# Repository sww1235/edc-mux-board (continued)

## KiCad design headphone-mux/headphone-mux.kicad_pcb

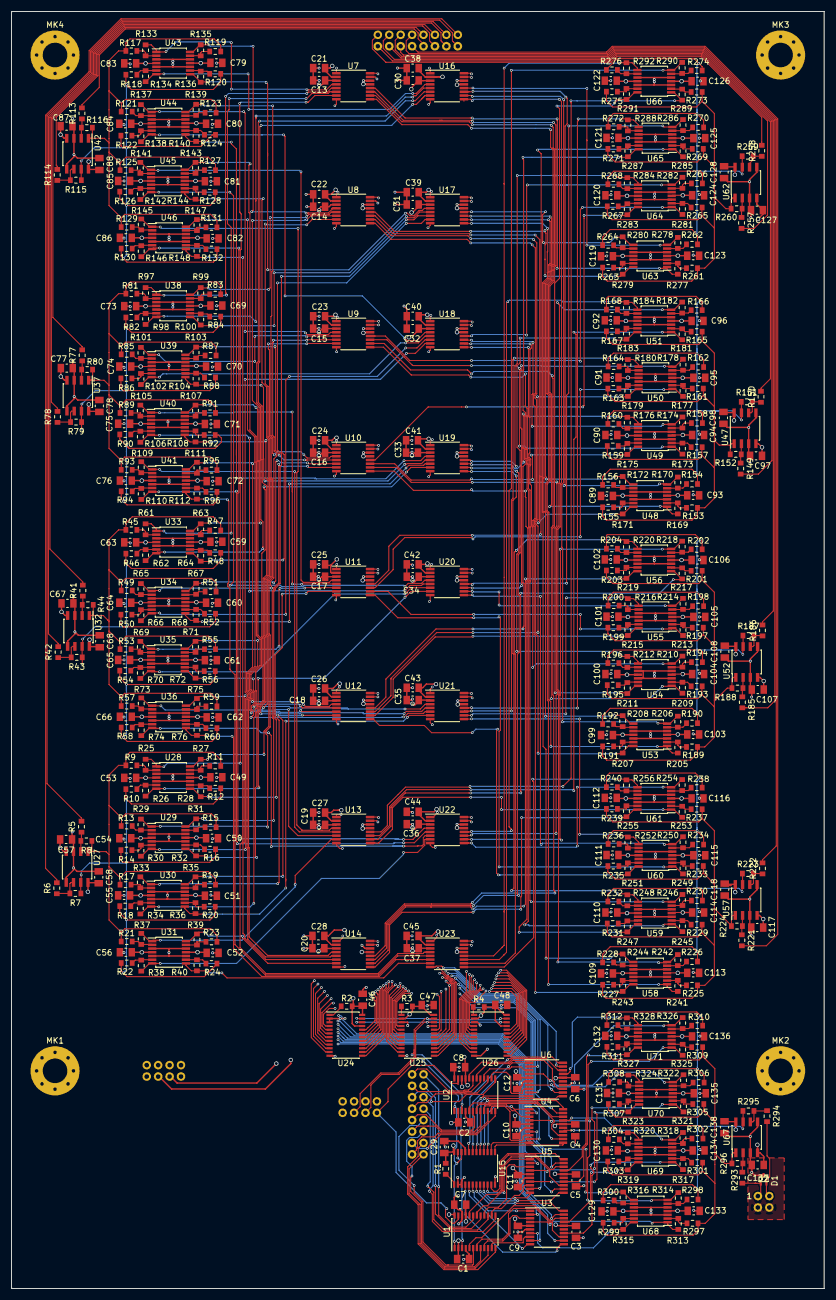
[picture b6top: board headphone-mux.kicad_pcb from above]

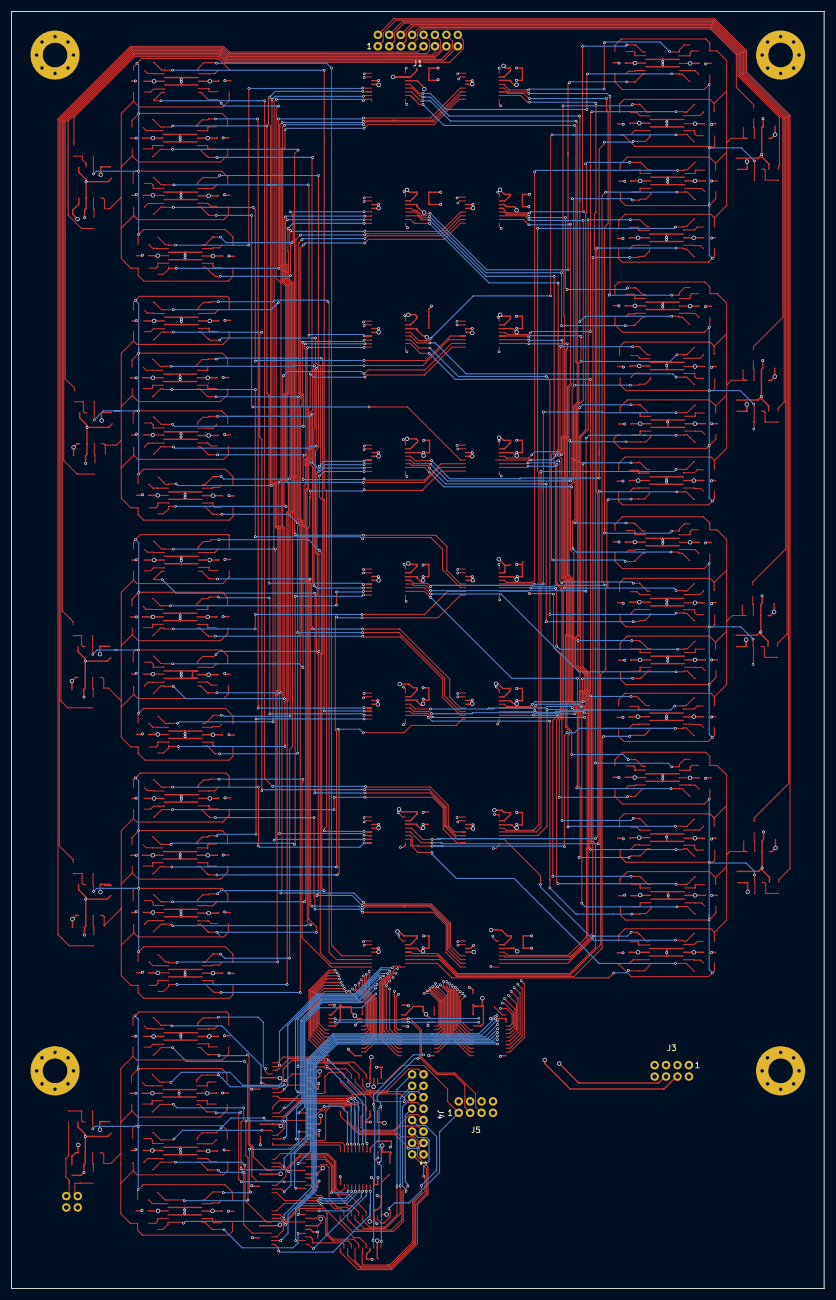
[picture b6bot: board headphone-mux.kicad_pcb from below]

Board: 4 copper layers, 142.2 x 223.5 mm, 547 parts (4 on the bottom side), 466 nets.

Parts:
C1, C2, C3, C4, C5, C6, C7, C8, C9, C10, C11, C12, C13, C14, C15, C16, C17, C18, C19, C20, C21, C22, C23, C24, C25, C26, C27, C28, C29, C30, C31, C32, C33, C34, C35, C36, C37, C38, C39, C40, C41, C42, C43, C44, C45, C46, C47, C48, C49, C50, C51, C52, C53, C54, C55, C56, C57, C58, C59, C60, C61, C62, C63, C64, C65, C66, C67, C68, C69, C70, C71, C72, C73, C74, C75, C76, C77, C78, C79, C80, C81, C82, C83, C84, C85, C86, C87, C88, C89, C90, C91, C92, C93, C94, C95, C96, C97, C98, C99, C100, C101, C102, C103, C104, C105, C106, C107, C108, C109, C110, C111, C112, C113, C114, C115, C116, C117, C118, C119, C120, C121, C122, C123, C124, C125, C126, C127, C128, C129, C130, C131, C132, C133, C134, C135, C136, C137, C138: 0.1uF; C_0805_2012Metric_Pad1.15x1.50mm_HandSolder
D1: 0582BQ; SC-75_3L
J1: Audio-Input; DF11-16DS-2DSA
J2: Mixer Audio In; DF11-4DP-2DSA
J3: Power Input; DF11-8DS-2DSA
J4: Audio Output; DF11-16DS-2DSA
J5: I2C and Reset; DF11-8DS-2DSA
MK1, MK2, MK3, MK4: Mounting_Hole_PAD; MountingHole_4.3mm_M4_Pad_Via
R1, R2, R3, R4: 10kΩ; R_0603_1608Metric_Pad0.84x1.00mm_HandSolder
R5, R6, R7, R8, R9, R10, R11, R12, R13, R14, R15, R16, R17, R18, R19, R20, R21, R22, R23, R24, R25, R26, R27, R28, R29, R30, R31, R32, R33, R34, R35, R36, R37, R38, R39, R40, R41, R42, R43, R44, R45, R46, R47, R48, R49, R50, R51, R52, R53, R54, R55, R56, R57, R58, R59, R60, R61, R62, R63, R64, R65, R66, R67, R68, R69, R70, R71, R72, R73, R74, R75, R76, R77, R78, R79, R80, R81, R82, R83, R84, R85, R86, R87, R88, R89, R90, R91, R92, R93, R94, R95, R96, R97, R98, R99, R100, R101, R102, R103, R104, R105, R106, R107, R108, R109, R110, R111, R112, R113, R114, R115, R116, R117, R118, R119, R120, R121, R122, R123, R124, R125, R126, R127, R128, R129, R130, R131, R132, R133, R134, R135, R136, R137, R138, R139, R140, R141, R142, R143, R144, R145, R146, R147, R148, R149, R150, R151, R152, R153, R154, R155, R156, R157, R158, R159, R160, R161, R162, R163, R164, R165, R166, R167, R168, R169, R170, R171, R172, R173, R174, R175, R176, R177, R178, R179, R180, R181, R182, R183, R184, R185, R186, R187, R188, R189, R190, R191, R192, R193, R194, R195, R196, R197, R198, R199, R200, R201, R202, R203, R204, R205, R206, R207, R208, R209, R210, R211, R212, R213, R214, R215, R216, R217, R218, R219, R220, R221, R222, R223, R224, R225, R226, R227, R228, R229, R230, R231, R232, R233, R234, R235, R236, R237, R238, R239, R240, R241, R242, R243, R244, R245, R246, R247, R248, R249, R250, R251, R252, R253, R254, R255, R256, R257, R258, R259, R260, R261, R262, R263, R264, R265, R266, R267, R268, R269, R270, R271, R272, R273, R274, R275, R276, R277, R278, R279, R280, R281, R282, R283, R284, R285, R286, R287, R288, R289, R290, R291, R292, R293, R294, R295, R296, R297, R298, R299, R300, R301, R302, R303, R304, R305, R306, R307, R308, R309, R310, R311, R312, R313, R314, R315, R316, R317, R318, R319, R320, R321, R322, R323, R324, R325, R326, R327, R328: 100kΩ; R_0603_1608Metric_Pad0.84x1.00mm_HandSolder
U1, U2: ADG715; TSSOP-24_4.4x7.8mm_P0.65mm
U3, U4, U5, U6: ADG734; TSSOP-20_4.4x6.5mm_P0.65mm
U7, U8, U9, U10, U11, U12, U13, U14, U16, U17, U18, U19, U20, U21, U22, U23: ADG708; TSSOP-16_4.4x5mm_P0.65mm
U15, U24, U25, U26: TCA9555; TSSOP-24_4.4x7.8mm_P0.65mm
U27, U32, U37, U42, U47, U52, U57, U62, U67: OPA1602; SOIC-8_3.9x4.9mm_P1.27mm
U28, U29, U30, U31, U33, U34, U35, U36, U38, U39, U40, U41, U43, U44, U45, U46, U48, U49, U50, U51, U53, U54, U55, U56, U58, U59, U60, U61, U63, U64, U65, U66, U68, U69, U70, U71: OPA1604; TSSOP-14_4.4x5mm_P0.65mm

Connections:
+2V5: C1.2, C2.2, C3.2, C4.2, C5.2, C6.2, C21.1, C22.1, C23.1, C24.1, C25.1, C26.1, C27.1, C28.1, C29.2, C38.1, C39.1, C40.1, C41.1, C42.1, C43.1, C44.1, C45.1, C46.2, C47.2, C48.2, J3.4, R1.1, R2.1, R3.1, R4.1, U1.2, U1.24, U2.2, U2.22, U3.16, U4.16, U5.16, U6.16, U7.2, U7.13, U8.2, U8.13, U9.2, U9.13, U10.2, U10.13, U11.2, U11.13, U12.2, U12.13, U13.2, U13.13, U14.2, U14.13, U15.24, U16.2, U16.13, U17.2, U17.13, U18.2, U18.13, U19.2, U19.13, U20.2, U20.13, U21.2, U21.13, U22.2, U22.13, U23.2, U23.13, U24.21, U24.24, U25.2, U25.24, U26.2, U26.21, U26.24
+12VA: C53.2, C54.2, C55.2, C56.2, C58.2, C63.2, C64.2, C65.2, C66.2, C68.2, C73.2, C74.2, C75.2, C76.2, C78.2, C83.2, C84.2, C85.2, C86.2, C88.2, C93.2, C94.2, C95.2, C96.2, C98.2, C103.2, C104.2, C105.2, C106.2, C108.2, C113.2, C114.2, C115.2, C116.2, C118.2, C123.2, C124.2, C125.2, C126.2, C128.2, C133.2, C134.2, C135.2, C136.2, C138.2, J3.2, U27.8, U28.4, U29.4, U30.4, U31.4, U32.8, U33.4, U34.4, U35.4, U36.4, U37.8, U38.4, U39.4, U40.4, U41.4, U42.8, U43.4, U44.4, U45.4, U46.4, U47.8, U48.4, U49.4, U50.4, U51.4, U52.8, U53.4, U54.4, U55.4, U56.4, U57.8, U58.4, U59.4, U60.4, U61.4, U62.8, U63.4, U64.4, U65.4, U66.4, U67.8, U68.4, U69.4, U70.4, U71.4
-2.5V: C7.1, C8.1, C9.1, C10.1, C11.1, C12.1, C13.2, C14.2, C15.2, C16.2, C17.2, C18.2, C19.2, C20.2, C30.2, C31.2, C32.2, C33.2, C34.2, C35.2, C36.2, C37.2, J3.6, U1.21, U2.21, U3.5, U4.5, U5.5, U6.5, U7.3, U8.3, U9.3, U10.3, U11.3, U12.3, U13.3, U14.3, U16.3, U17.3, U18.3, U19.3, U20.3, U21.3, U22.3, U23.3
-12VA: C49.2, C50.2, C51.2, C52.2, C57.2, C59.2, C60.2, C61.2, C62.2, C67.2, C69.2, C70.2, C71.2, C72.2, C77.2, C79.2, C80.2, C81.2, C82.2, C87.2, C89.2, C90.2, C91.2, C92.2, C97.2, C99.2, C100.2, C101.2, C102.2, C107.2, C109.2, C110.2, C111.2, C112.2, C117.2, C119.2, C120.2, C121.2, C122.2, C127.2, C129.2, C130.2, C131.2, C132.2, C137.2, J3.8, U27.4, U28.11, U29.11, U30.11, U31.11, U32.4, U33.11, U34.11, U35.11, U36.11, U37.4, U38.11, U39.11, U40.11, U41.11, U42.4, U43.11, U44.11, U45.11, U46.11, U47.4, U48.11, U49.11, U50.11, U51.11, U52.4, U53.11, U54.11, U55.11, U56.11, U57.4, U58.11, U59.11, U60.11, U61.11, U62.4, U63.11, U64.11, U65.11, U66.11, U67.4, U68.11, U69.11, U70.11, U71.11
/2v5-SCL-0: J5.3, U1.1, U2.1, U15.22, U24.22, U25.22, U26.22
/2v5-SDA-0: J5.5, U1.3, U2.3, U15.23, U24.23, U25.23, U26.23
/HEADSET-AUDIO-SOURCE-L-0: J1.1, R5.2
/HEADSET-AUDIO-SOURCE-L-1: J1.3, R41.2
/HEADSET-AUDIO-SOURCE-L-2: J1.5, R77.2
/HEADSET-AUDIO-SOURCE-L-3: J1.7, R113.2
/HEADSET-AUDIO-SOURCE-L-4: J1.15, R257.2
/HEADSET-AUDIO-SOURCE-L-5: J1.13, R149.2
/HEADSET-AUDIO-SOURCE-L-6: J1.11, R185.2
/HEADSET-AUDIO-SOURCE-L-7: J1.9, R221.2
/HEADSET-AUDIO-SOURCE-R-0: J1.2, R6.2
/HEADSET-AUDIO-SOURCE-R-1: J1.4, R42.2
/HEADSET-AUDIO-SOURCE-R-2: J1.6, R78.2
/HEADSET-AUDIO-SOURCE-R-3: J1.8, R114.2
/HEADSET-AUDIO-SOURCE-R-4: J1.16, R258.2
/HEADSET-AUDIO-SOURCE-R-5: J1.14, R150.2
/HEADSET-AUDIO-SOURCE-R-6: J1.12, R186.2
/HEADSET-AUDIO-SOURCE-R-7: J1.10, R222.2
/Headset Audio Out Mux Switching/DEV0_L_0: R25.1, U7.7, U28.1
/Headset Audio Out Mux Switching/DEV0_L_1: R27.1, U8.7, U28.14
/Headset Audio Out Mux Switching/DEV0_L_2: R29.1, U9.7, U29.1
/Headset Audio Out Mux Switching/DEV0_L_3: R31.1, U10.7, U29.14
/Headset Audio Out Mux Switching/DEV0_L_4: R33.1, U11.7, U30.1
/Headset Audio Out Mux Switching/DEV0_L_5: R35.1, U12.7, U30.14
/Headset Audio Out Mux Switching/DEV0_L_6: R37.1, U13.7, U31.1
/Headset Audio Out Mux Switching/DEV0_L_7: R39.1, U14.7, U31.14
/Headset Audio Out Mux Switching/DEV0_R_0: R26.1, U16.7, U28.7
/Headset Audio Out Mux Switching/DEV0_R_1: R28.1, U17.7, U28.8
/Headset Audio Out Mux Switching/DEV0_R_2: R30.1, U18.7, U29.7
/Headset Audio Out Mux Switching/DEV0_R_3: R32.1, U19.7, U29.8
/Headset Audio Out Mux Switching/DEV0_R_4: R34.1, U20.7, U30.7
/Headset Audio Out Mux Switching/DEV0_R_5: R36.1, U21.7, U30.8
/Headset Audio Out Mux Switching/DEV0_R_6: R38.1, U22.7, U31.7
/Headset Audio Out Mux Switching/DEV0_R_7: R40.1, U23.7, U31.8
/Headset Audio Out Mux Switching/DEV1_L_0: R61.1, U7.6, U33.1
/Headset Audio Out Mux Switching/DEV1_L_1: R63.1, U8.6, U33.14
/Headset Audio Out Mux Switching/DEV1_L_2: R65.1, U9.6, U34.1
/Headset Audio Out Mux Switching/DEV1_L_3: R67.1, U10.6, U34.14
/Headset Audio Out Mux Switching/DEV1_L_4: R69.1, U11.6, U35.1
/Headset Audio Out Mux Switching/DEV1_L_5: R71.1, U12.6, U35.14
/Headset Audio Out Mux Switching/DEV1_L_6: R73.1, U13.6, U36.1
/Headset Audio Out Mux Switching/DEV1_L_7: R75.1, U14.6, U36.14
/Headset Audio Out Mux Switching/DEV1_R_0: R62.1, U16.6, U33.7
/Headset Audio Out Mux Switching/DEV1_R_1: R64.1, U17.6, U33.8
/Headset Audio Out Mux Switching/DEV1_R_2: R66.1, U18.6, U34.7
/Headset Audio Out Mux Switching/DEV1_R_3: R68.1, U19.6, U34.8
/Headset Audio Out Mux Switching/DEV1_R_4: R70.1, U20.6, U35.7
/Headset Audio Out Mux Switching/DEV1_R_5: R72.1, U21.6, U35.8
/Headset Audio Out Mux Switching/DEV1_R_6: R74.1, U22.6, U36.7
/Headset Audio Out Mux Switching/DEV1_R_7: R76.1, U23.6, U36.8
/Headset Audio Out Mux Switching/DEV2_L_0: R97.1, U7.5, U38.1
/Headset Audio Out Mux Switching/DEV2_L_1: R99.1, U8.5, U38.14
/Headset Audio Out Mux Switching/DEV2_L_2: R101.1, U9.5, U39.1
/Headset Audio Out Mux Switching/DEV2_L_3: R103.1, U10.5, U39.14
/Headset Audio Out Mux Switching/DEV2_L_4: R105.1, U11.5, U40.1
/Headset Audio Out Mux Switching/DEV2_L_5: R107.1, U12.5, U40.14
/Headset Audio Out Mux Switching/DEV2_L_6: R109.1, U13.5, U41.1
/Headset Audio Out Mux Switching/DEV2_L_7: R111.1, U14.5, U41.14
/Headset Audio Out Mux Switching/DEV2_R_0: R98.1, U16.5, U38.7
/Headset Audio Out Mux Switching/DEV2_R_1: R100.1, U17.5, U38.8
/Headset Audio Out Mux Switching/DEV2_R_2: R102.1, U18.5, U39.7
/Headset Audio Out Mux Switching/DEV2_R_3: R104.1, U19.5, U39.8
/Headset Audio Out Mux Switching/DEV2_R_4: R106.1, U20.5, U40.7
/Headset Audio Out Mux Switching/DEV2_R_5: R108.1, U21.5, U40.8
/Headset Audio Out Mux Switching/DEV2_R_6: R110.1, U22.5, U41.7
/Headset Audio Out Mux Switching/DEV2_R_7: R112.1, U23.5, U41.8
/Headset Audio Out Mux Switching/DEV3_L_0: R133.1, U7.4, U43.1
/Headset Audio Out Mux Switching/DEV3_L_1: R135.1, U8.4, U43.14
/Headset Audio Out Mux Switching/DEV3_L_2: R137.1, U9.4, U44.1
/Headset Audio Out Mux Switching/DEV3_L_3: R139.1, U10.4, U44.14
/Headset Audio Out Mux Switching/DEV3_L_4: R141.1, U11.4, U45.1
/Headset Audio Out Mux Switching/DEV3_L_5: R143.1, U12.4, U45.14
/Headset Audio Out Mux Switching/DEV3_L_6: R145.1, U13.4, U46.1
/Headset Audio Out Mux Switching/DEV3_L_7: R147.1, U14.4, U46.14
/Headset Audio Out Mux Switching/DEV3_R_0: R134.1, U16.4, U43.7
/Headset Audio Out Mux Switching/DEV3_R_1: R136.1, U17.4, U43.8
/Headset Audio Out Mux Switching/DEV3_R_2: R138.1, U18.4, U44.7
/Headset Audio Out Mux Switching/DEV3_R_3: R140.1, U19.4, U44.8
/Headset Audio Out Mux Switching/DEV3_R_4: R142.1, U20.4, U45.7
/Headset Audio Out Mux Switching/DEV3_R_5: R144.1, U21.4, U45.8
/Headset Audio Out Mux Switching/DEV3_R_6: R146.1, U22.4, U46.7
/Headset Audio Out Mux Switching/DEV3_R_7: R148.1, U23.4, U46.8
/Headset Audio Out Mux Switching/DEV4_L_0: R277.1, U7.12, U63.1
/Headset Audio Out Mux Switching/DEV4_L_1: R279.1, U8.12, U63.14
/Headset Audio Out Mux Switching/DEV4_L_2: R281.1, U9.12, U64.1
/Headset Audio Out Mux Switching/DEV4_L_3: R283.1, U10.12, U64.14
/Headset Audio Out Mux Switching/DEV4_L_4: R285.1, U11.12, U65.1
/Headset Audio Out Mux Switching/DEV4_L_5: R287.1, U12.12, U65.14
/Headset Audio Out Mux Switching/DEV4_L_6: R289.1, U13.12, U66.1
/Headset Audio Out Mux Switching/DEV4_L_7: R291.1, U14.12, U66.14
/Headset Audio Out Mux Switching/DEV4_R_0: R278.1, U16.12, U63.7
/Headset Audio Out Mux Switching/DEV4_R_1: R280.1, U17.12, U63.8
/Headset Audio Out Mux Switching/DEV4_R_2: R282.1, U18.12, U64.7
/Headset Audio Out Mux Switching/DEV4_R_3: R284.1, U19.12, U64.8
/Headset Audio Out Mux Switching/DEV4_R_4: R286.1, U20.12, U65.7
/Headset Audio Out Mux Switching/DEV4_R_5: R288.1, U21.12, U65.8
/Headset Audio Out Mux Switching/DEV4_R_6: R290.1, U22.12, U66.7
/Headset Audio Out Mux Switching/DEV4_R_7: R292.1, U23.12, U66.8
/Headset Audio Out Mux Switching/DEV5_L_0: R169.1, U7.11, U48.1
/Headset Audio Out Mux Switching/DEV5_L_1: R171.1, U8.11, U48.14
/Headset Audio Out Mux Switching/DEV5_L_2: R173.1, U9.11, U49.1
/Headset Audio Out Mux Switching/DEV5_L_3: R175.1, U10.11, U49.14
/Headset Audio Out Mux Switching/DEV5_L_4: R177.1, U11.11, U50.1
/Headset Audio Out Mux Switching/DEV5_L_5: R179.1, U12.11, U50.14
/Headset Audio Out Mux Switching/DEV5_L_6: R181.1, U13.11, U51.1
/Headset Audio Out Mux Switching/DEV5_L_7: R183.1, U14.11, U51.14
/Headset Audio Out Mux Switching/DEV5_R_0: R170.1, U16.11, U48.7
/Headset Audio Out Mux Switching/DEV5_R_1: R172.1, U17.11, U48.8
/Headset Audio Out Mux Switching/DEV5_R_2: R174.1, U18.11, U49.7
/Headset Audio Out Mux Switching/DEV5_R_3: R176.1, U19.11, U49.8
/Headset Audio Out Mux Switching/DEV5_R_4: R178.1, U20.11, U50.7
/Headset Audio Out Mux Switching/DEV5_R_5: R180.1, U21.11, U50.8
/Headset Audio Out Mux Switching/DEV5_R_6: R182.1, U22.11, U51.7
/Headset Audio Out Mux Switching/DEV5_R_7: R184.1, U23.11, U51.8
/Headset Audio Out Mux Switching/DEV6_L_0: R205.1, U7.10, U53.1
/Headset Audio Out Mux Switching/DEV6_L_1: R207.1, U8.10, U53.14
/Headset Audio Out Mux Switching/DEV6_L_2: R209.1, U9.10, U54.1
/Headset Audio Out Mux Switching/DEV6_L_3: R211.1, U10.10, U54.14
/Headset Audio Out Mux Switching/DEV6_L_4: R213.1, U11.10, U55.1
/Headset Audio Out Mux Switching/DEV6_L_5: R215.1, U12.10, U55.14
/Headset Audio Out Mux Switching/DEV6_L_6: R217.1, U13.10, U56.1
/Headset Audio Out Mux Switching/DEV6_L_7: R219.1, U14.10, U56.14
/Headset Audio Out Mux Switching/DEV6_R_0: R206.1, U16.10, U53.7
/Headset Audio Out Mux Switching/DEV6_R_1: R208.1, U17.10, U53.8
/Headset Audio Out Mux Switching/DEV6_R_2: R210.1, U18.10, U54.7
/Headset Audio Out Mux Switching/DEV6_R_3: R212.1, U19.10, U54.8
/Headset Audio Out Mux Switching/DEV6_R_4: R214.1, U20.10, U55.7
/Headset Audio Out Mux Switching/DEV6_R_5: R216.1, U21.10, U55.8
/Headset Audio Out Mux Switching/DEV6_R_6: R218.1, U22.10, U56.7
/Headset Audio Out Mux Switching/DEV6_R_7: R220.1, U23.10, U56.8
/Headset Audio Out Mux Switching/DEV7_L_0: R241.1, U7.9, U58.1
/Headset Audio Out Mux Switching/DEV7_L_1: R243.1, U8.9, U58.14
/Headset Audio Out Mux Switching/DEV7_L_2: R245.1, U9.9, U59.1
/Headset Audio Out Mux Switching/DEV7_L_3: R247.1, U10.9, U59.14
/Headset Audio Out Mux Switching/DEV7_L_4: R249.1, U11.9, U60.1
/Headset Audio Out Mux Switching/DEV7_L_5: R251.1, U12.9, U60.14
/Headset Audio Out Mux Switching/DEV7_L_6: R253.1, U13.9, U61.1
/Headset Audio Out Mux Switching/DEV7_L_7: R255.1, U14.9, U61.14
/Headset Audio Out Mux Switching/DEV7_R_0: R242.1, U16.9, U58.7
/Headset Audio Out Mux Switching/DEV7_R_1: R244.1, U17.9, U58.8
/Headset Audio Out Mux Switching/DEV7_R_2: R246.1, U18.9, U59.7
/Headset Audio Out Mux Switching/DEV7_R_3: R248.1, U19.9, U59.8
/Headset Audio Out Mux Switching/DEV7_R_4: R250.1, U20.9, U60.7
/Headset Audio Out Mux Switching/DEV7_R_5: R252.1, U21.9, U60.8
/Headset Audio Out Mux Switching/DEV7_R_6: R254.1, U22.9, U61.7
/Headset Audio Out Mux Switching/DEV7_R_7: R256.1, U23.9, U61.8
/Headset Audio Out Mux Switching/DEV_XBAR_CTL0: U7.1, U24.11
/Headset Audio Out Mux Switching/DEV_XBAR_CTL1: U7.16, U25.4
/Headset Audio Out Mux Switching/DEV_XBAR_CTL2: U7.15, U25.5
/Headset Audio Out Mux Switching/DEV_XBAR_CTL3: U8.1, U24.10
/Headset Audio Out Mux Switching/DEV_XBAR_CTL4: U8.16, U25.6
/Headset Audio Out Mux Switching/DEV_XBAR_CTL5: U8.15, U25.7
/Headset Audio Out Mux Switching/DEV_XBAR_CTL6: U9.1, U24.9
/Headset Audio Out Mux Switching/DEV_XBAR_CTL7: U9.16, U25.8
/Headset Audio Out Mux Switching/DEV_XBAR_CTL8: U9.15, U25.9
/Headset Audio Out Mux Switching/DEV_XBAR_CTL9: U10.1, U24.8
/Headset Audio Out Mux Switching/DEV_XBAR_CTL10: U10.16, U25.10
/Headset Audio Out Mux Switching/DEV_XBAR_CTL11: U10.15, U25.11
/Headset Audio Out Mux Switching/DEV_XBAR_CTL12: U11.1, U24.7
/Headset Audio Out Mux Switching/DEV_XBAR_CTL13: U11.16, U24.13
/Headset Audio Out Mux Switching/DEV_XBAR_CTL14: U11.15, U24.14
/Headset Audio Out Mux Switching/DEV_XBAR_CTL15: U12.1, U24.6
/Headset Audio Out Mux Switching/DEV_XBAR_CTL16: U12.16, U24.15
/Headset Audio Out Mux Switching/DEV_XBAR_CTL17: U12.15, U24.16
/Headset Audio Out Mux Switching/DEV_XBAR_CTL18: U13.1, U24.5
/Headset Audio Out Mux Switching/DEV_XBAR_CTL19: U13.16, U24.17
/Headset Audio Out Mux Switching/DEV_XBAR_CTL20: U13.15, U24.18
/Headset Audio Out Mux Switching/DEV_XBAR_CTL21: U14.1, U24.4
/Headset Audio Out Mux Switching/DEV_XBAR_CTL22: U14.16, U24.19
/Headset Audio Out Mux Switching/DEV_XBAR_CTL23: U14.15, U24.20
/Headset Audio Out Mux Switching/DEV_XBAR_CTL24: U16.1, U25.20
/Headset Audio Out Mux Switching/DEV_XBAR_CTL25: U16.16, U26.13
/Headset Audio Out Mux Switching/DEV_XBAR_CTL26: U16.15, U26.14
/Headset Audio Out Mux Switching/DEV_XBAR_CTL27: U17.1, U25.19
/Headset Audio Out Mux Switching/DEV_XBAR_CTL28: U17.16, U26.15
/Headset Audio Out Mux Switching/DEV_XBAR_CTL29: U17.15, U26.16
/Headset Audio Out Mux Switching/DEV_XBAR_CTL30: U18.1, U25.18
/Headset Audio Out Mux Switching/DEV_XBAR_CTL31: U18.16, U26.17
/Headset Audio Out Mux Switching/DEV_XBAR_CTL32: U18.15, U26.18
/Headset Audio Out Mux Switching/DEV_XBAR_CTL33: U19.1, U25.17
/Headset Audio Out Mux Switching/DEV_XBAR_CTL34: U19.16, U26.19
/Headset Audio Out Mux Switching/DEV_XBAR_CTL35: U19.15, U26.20
/Headset Audio Out Mux Switching/DEV_XBAR_CTL36: U20.1, U25.16
/Headset Audio Out Mux Switching/DEV_XBAR_CTL37: U20.16, U26.4
/Headset Audio Out Mux Switching/DEV_XBAR_CTL38: U20.15, U26.5
/Headset Audio Out Mux Switching/DEV_XBAR_CTL39: U21.1, U25.15
/Headset Audio Out Mux Switching/DEV_XBAR_CTL40: U21.16, U26.6
/Headset Audio Out Mux Switching/DEV_XBAR_CTL41: U21.15, U26.7
/Headset Audio Out Mux Switching/DEV_XBAR_CTL42: U22.1, U25.14
/Headset Audio Out Mux Switching/DEV_XBAR_CTL43: U22.16, U26.8
/Headset Audio Out Mux Switching/DEV_XBAR_CTL44: U22.15, U26.9
/Headset Audio Out Mux Switching/DEV_XBAR_CTL45: U23.1, U25.13
/Headset Audio Out Mux Switching/DEV_XBAR_CTL46: U23.16, U26.10
/Headset Audio Out Mux Switching/DEV_XBAR_CTL47: U23.15, U26.11
/Headset Audio Out Mux Switching/Dev 0 1:8 DA/L_Distro_Bus: R8.1, R9.2, R11.2, R13.2, R15.2, R17.2, R19.2, R21.2, R23.2, U27.1
/Headset Audio Out Mux Switching/Dev 0 1:8 DA/R_Distro_Bus: R7.1, R10.2, R12.2, R14.2, R16.2, R18.2, R20.2, R22.2, R24.2, U27.7
/Headset Audio Out Mux Switching/Dev 1 1:8 DA/L_Distro_Bus: R44.1, R45.2, R47.2, R49.2, R51.2, R53.2, R55.2, R57.2, R59.2, U32.1
/Headset Audio Out Mux Switching/Dev 1 1:8 DA/R_Distro_Bus: R43.1, R46.2, R48.2, R50.2, R52.2, R54.2, R56.2, R58.2, R60.2, U32.7
/Headset Audio Out Mux Switching/Dev 2 1:8 DA/L_Distro_Bus: R80.1, R81.2, R83.2, R85.2, R87.2, R89.2, R91.2, R93.2, R95.2, U37.1
/Headset Audio Out Mux Switching/Dev 2 1:8 DA/R_Distro_Bus: R79.1, R82.2, R84.2, R86.2, R88.2, R90.2, R92.2, R94.2, R96.2, U37.7
/Headset Audio Out Mux Switching/Dev 3 1:8 DA/L_Distro_Bus: R116.1, R117.2, R119.2, R121.2, R123.2, R125.2, R127.2, R129.2, R131.2, U42.1
/Headset Audio Out Mux Switching/Dev 3 1:8 DA/R_Distro_Bus: R115.1, R118.2, R120.2, R122.2, R124.2, R126.2, R128.2, R130.2, R132.2, U42.7
/Headset Audio Out Mux Switching/Dev 4 1:8 DA/L_Distro_Bus: R260.1, R261.2, R263.2, R265.2, R267.2, R269.2, R271.2, R273.2, R275.2, U62.1
/Headset Audio Out Mux Switching/Dev 4 1:8 DA/R_Distro_Bus: R259.1, R262.2, R264.2, R266.2, R268.2, R270.2, R272.2, R274.2, R276.2, U62.7
/Headset Audio Out Mux Switching/Dev 5 1:8 DA/L_Distro_Bus: R152.1, R153.2, R155.2, R157.2, R159.2, R161.2, R163.2, R165.2, R167.2, U47.1
/Headset Audio Out Mux Switching/Dev 5 1:8 DA/R_Distro_Bus: R151.1, R154.2, R156.2, R158.2, R160.2, R162.2, R164.2, R166.2, R168.2, U47.7
/Headset Audio Out Mux Switching/Dev 6 1:8 DA/L_Distro_Bus: R188.1, R189.2, R191.2, R193.2, R195.2, R197.2, R199.2, R201.2, R203.2, U52.1
/Headset Audio Out Mux Switching/Dev 6 1:8 DA/R_Distro_Bus: R187.1, R190.2, R192.2, R194.2, R196.2, R198.2, R200.2, R202.2, R204.2, U52.7
/Headset Audio Out Mux Switching/Dev 7 1:8 DA/L_Distro_Bus: R224.1, R225.2, R227.2, R229.2, R231.2, R233.2, R235.2, R237.2, R239.2, U57.1
/Headset Audio Out Mux Switching/Dev 7 1:8 DA/R_Distro_Bus: R223.1, R226.2, R228.2, R230.2, R232.2, R234.2, R236.2, R238.2, R240.2, U57.7
/Headset Audio Out Mux Switching/MIDL0: U3.2, U7.8
/Headset Audio Out Mux Switching/MIDL1: U3.9, U8.8
/Headset Audio Out Mux Switching/MIDL2: U3.12, U9.8
/Headset Audio Out Mux Switching/MIDL3: U3.19, U10.8
/Headset Audio Out Mux Switching/MIDL4: U5.2, U11.8
/Headset Audio Out Mux Switching/MIDL5: U5.9, U12.8
/Headset Audio Out Mux Switching/MIDL6: U5.12, U13.8
/Headset Audio Out Mux Switching/MIDL7: U5.19, U14.8
/Headset Audio Out Mux Switching/MIDR0: U4.2, U16.8
/Headset Audio Out Mux Switching/MIDR1: U4.9, U17.8
/Headset Audio Out Mux Switching/MIDR2: U4.12, U18.8
/Headset Audio Out Mux Switching/MIDR3: U4.19, U19.8
/Headset Audio Out Mux Switching/MIDR4: U6.2, U20.8
/Headset Audio Out Mux Switching/MIDR5: U6.9, U21.8
/Headset Audio Out Mux Switching/MIDR6: U6.12, U22.8
/Headset Audio Out Mux Switching/MIDR7: U6.19, U23.8
/Headset Audio Out Mux Switching/MIXER_L_IN: D1.1, J2.1, R293.2
/Headset Audio Out Mux Switching/MIXER_OUT_L0: R313.1, U3.4, U68.1
/Headset Audio Out Mux Switching/MIXER_OUT_L1: R315.1, U3.7, U68.14
/Headset Audio Out Mux Switching/MIXER_OUT_L2: R317.1, U3.14, U69.1
/Headset Audio Out Mux Switching/MIXER_OUT_L3: R319.1, U3.17, U69.14
/Headset Audio Out Mux Switching/MIXER_OUT_L4: R321.1, U5.4, U70.1
/Headset Audio Out Mux Switching/MIXER_OUT_L5: R323.1, U5.7, U70.14
/Headset Audio Out Mux Switching/MIXER_OUT_L6: R325.1, U5.14, U71.1
/Headset Audio Out Mux Switching/MIXER_OUT_L7: R327.1, U5.17, U71.14
/Headset Audio Out Mux Switching/MIXER_OUT_R0: R314.1, U4.4, U68.7
/Headset Audio Out Mux Switching/MIXER_OUT_R1: R316.1, U4.7, U68.8
/Headset Audio Out Mux Switching/MIXER_OUT_R2: R318.1, U4.14, U69.7
/Headset Audio Out Mux Switching/MIXER_OUT_R3: R320.1, U4.17, U69.8
/Headset Audio Out Mux Switching/MIXER_OUT_R4: R322.1, U6.4, U70.7
/Headset Audio Out Mux Switching/MIXER_OUT_R5: R324.1, U6.7, U70.8
/Headset Audio Out Mux Switching/MIXER_OUT_R6: R326.1, U6.14, U71.7
/Headset Audio Out Mux Switching/MIXER_OUT_R7: R328.1, U6.17, U71.8
/Headset Audio Out Mux Switching/MIXER_R_IN: D1.2, J2.3, R294.2
/Headset Audio Out Mux Switching/Mixer Out 1:8 DA/L_Distro_Bus: R296.1, R297.2, R299.2, R301.2, R303.2, R305.2, R307.2, R309.2, R311.2, U67.1
/Headset Audio Out Mux Switching/Mixer Out 1:8 DA/R_Distro_Bus: R295.1, R298.2, R300.2, R302.2, R304.2, R306.2, R308.2, R310.2, R312.2, U67.7
/Headset Audio Out Mux Switching/SPDT_CTL0: U3.1, U15.6
/Headset Audio Out Mux Switching/SPDT_CTL1: U4.1, U15.15
/Headset Audio Out Mux Switching/SPDT_CTL2: U3.10, U15.5
/Headset Audio Out Mux Switching/SPDT_CTL3: U4.10, U15.14
/Headset Audio Out Mux Switching/SPDT_CTL4: U3.11, U15.4
/Headset Audio Out Mux Switching/SPDT_CTL5: U4.11, U15.13
/Headset Audio Out Mux Switching/SPDT_CTL6: U3.20, U15.7
/Headset Audio Out Mux Switching/SPDT_CTL7: U4.20, U15.16
/Headset Audio Out Mux Switching/SPDT_CTL8: U5.1, U15.10
/Headset Audio Out Mux Switching/SPDT_CTL9: U6.1, U15.19
/Headset Audio Out Mux Switching/SPDT_CTL10: U5.10, U15.9
/Headset Audio Out Mux Switching/SPDT_CTL11: U6.10, U15.18
/Headset Audio Out Mux Switching/SPDT_CTL12: U5.11, U15.8
/Headset Audio Out Mux Switching/SPDT_CTL13: U6.11, U15.17
/Headset Audio Out Mux Switching/SPDT_CTL14: U5.20, U15.11
/Headset Audio Out Mux Switching/SPDT_CTL15: U6.20, U15.20
/L_OUT0: U1.9, U3.3
/L_OUT1: U1.11, U3.8
/L_OUT2: U1.7, U3.13
/L_OUT3: U1.5, U3.18
/L_OUT4: U1.16, U5.3
/L_OUT5: U1.14, U5.8
/L_OUT6: U1.18, U5.13
/L_OUT7: U1.20, U5.18
/R_OUT0: U2.9, U4.3
/R_OUT1: U2.11, U4.8
/R_OUT2: U2.7, U4.13
/R_OUT3: U2.5, U4.18
/R_OUT4: U2.16, U6.3
/R_OUT5: U2.14, U6.8
/R_OUT6: U2.18, U6.13
/R_OUT7: U2.20, U6.18
/SPST_~RST: J5.1, U1.23, U2.23
GNDREF: C1.1, C2.1, C3.1, C4.1, C5.1, C6.1, C7.2, C8.2, C9.2, C10.2, C11.2, C12.2, C13.1, C14.1, C15.1, C16.1, C17.1, C18.1, C19.1, C20.1, C21.2, C22.2, C23.2, C24.2, C25.2, C26.2, C27.2, C28.2, C29.1, C30.1, C31.1, C32.1, C33.1, C34.1, C35.1, C36.1, C37.1, C38.2, C39.2, C40.2, C41.2, C42.2, C43.2, C44.2, C45.2, C46.1, C47.1, C48.1, C49.1, C50.1, C51.1, C52.1, C53.1, C54.1, C55.1, C56.1, C57.1, C58.1, C59.1, C60.1, C61.1, C62.1, C63.1, C64.1, C65.1, C66.1, C67.1, C68.1, C69.1, C70.1, C71.1, C72.1, C73.1, C74.1, C75.1, C76.1, C77.1, C78.1, C79.1, C80.1, C81.1, C82.1, C83.1, C84.1, C85.1, C86.1, C87.1, C88.1, C89.1, C90.1, C91.1, C92.1, C93.1, C94.1, C95.1, C96.1, C97.1, C98.1, C99.1, C100.1, C101.1, C102.1, C103.1, C104.1, C105.1, C106.1, C107.1, C108.1, C109.1, C110.1, C111.1, C112.1, C113.1, C114.1, C115.1, C116.1, C117.1, C118.1, C119.1, C120.1, C121.1, C122.1, C123.1, C124.1, C125.1, C126.1, C127.1, C128.1, C129.1, C130.1, C131.1, C132.1, C133.1, C134.1, C135.1, C136.1, C137.1, C138.1, D1.3, J2.2, J2.4, J3.1, J3.3, J3.5, J3.7, J5.2, J5.4, J5.6, J5.7, J5.8, MK1.1, MK2.1, MK3.1, MK4.1, U1.4, U1.22, U2.4, U2.24, U3.6, U4.6, U5.6, U6.6, U7.14, U8.14, U9.14, U10.14, U11.14, U12.14, U13.14, U14.14, U15.2, U15.3, U15.12, U15.21, U16.14, U17.14, U18.14, U19.14, U20.14, U21.14, U22.14, U23.14, U24.2, U24.3, U24.12, U25.3, U25.12, U25.21, U26.3, U26.12, U27.3, U27.5, U28.3, U28.5, U28.10, U28.12, U29.3, U29.5, U29.10, U29.12, U30.3, U30.5, U30.10, U30.12, U31.3, U31.5, U31.10, U31.12, U32.3, U32.5, U33.3, U33.5, U33.10, U33.12, U34.3, U34.5, U34.10, U34.12, U35.3, U35.5, U35.10, U35.12, U36.3, U36.5, U36.10, U36.12, U37.3, U37.5, U38.3, U38.5, U38.10, U38.12, U39.3, U39.5, U39.10, U39.12, U40.3, U40.5, U40.10, U40.12, U41.3, U41.5, U41.10, U41.12, U42.3, U42.5, U43.3, U43.5, U43.10, U43.12, U44.3, U44.5, U44.10, U44.12, U45.3, U45.5, U45.10, U45.12, U46.3, U46.5, U46.10, U46.12, U47.3, U47.5, U48.3, U48.5, U48.10, U48.12, U49.3, U49.5, U49.10, U49.12, U50.3, U50.5, U50.10, U50.12, U51.3, U51.5, U51.10, U51.12, U52.3, U52.5, U53.3, U53.5, U53.10, U53.12, U54.3, U54.5, U54.10, U54.12, U55.3, U55.5, U55.10, U55.12, U56.3, U56.5, U56.10, U56.12, U57.3, U57.5, U58.3, U58.5, U58.10, U58.12, U59.3, U59.5, U59.10, U59.12, U60.3, U60.5, U60.10, U60.12, U61.3, U61.5, U61.10, U61.12, U62.3, U62.5, U63.3, U63.5, U63.10, U63.12, U64.3, U64.5, U64.10, U64.12, U65.3, U65.5, U65.10, U65.12, U66.3, U66.5, U66.10, U66.12, U67.3, U67.5, U68.3, U68.5, U68.10, U68.12, U69.3, U69.5, U69.10, U69.12, U70.3, U70.5, U70.10, U70.12, U71.3, U71.5, U71.10, U71.12
unnamed: J4.1, U2.10
unnamed: J4.2, U1.10
unnamed: J4.3, U2.12
unnamed: J4.4, U1.12
unnamed: J4.5, U2.8
unnamed: J4.6, U1.8
unnamed: J4.7, U2.6
unnamed: J4.8, U1.6
unnamed: J4.9, U2.15
unnamed: J4.10, U1.15
unnamed: J4.11, U2.13
unnamed: J4.12, U1.13
unnamed: J4.13, U2.17
unnamed: J4.14, U1.17
unnamed: J4.15, U2.19
unnamed: J4.16, U1.19
unnamed: R1.2, U15.1
unnamed: R2.2, U24.1
unnamed: R3.2, U25.1
unnamed: R4.2, U26.1
unnamed: R5.1, R8.2, U27.2
unnamed: R6.1, R7.2, U27.6
unnamed: R10.1, R26.2, U28.6
unnamed: R11.1, R27.2, U28.13
unnamed: R12.1, R28.2, U28.9
unnamed: R13.1, R29.2, U29.2
unnamed: R14.1, R30.2, U29.6
unnamed: R15.1, R31.2, U29.13
unnamed: R16.1, R32.2, U29.9
unnamed: R17.1, R33.2, U30.2
unnamed: R18.1, R34.2, U30.6
unnamed: R19.1, R35.2, U30.13
unnamed: R20.1, R36.2, U30.9
unnamed: R21.1, R37.2, U31.2
unnamed: R22.1, R38.2, U31.6
unnamed: R23.1, R39.2, U31.13
unnamed: R24.1, R40.2, U31.9
unnamed: R9.1, R25.2, U28.2
unnamed: R41.1, R44.2, U32.2
unnamed: R42.1, R43.2, U32.6
unnamed: R45.1, R61.2, U33.2
unnamed: R46.1, R62.2, U33.6
unnamed: R47.1, R63.2, U33.13
unnamed: R48.1, R64.2, U33.9
unnamed: R49.1, R65.2, U34.2
unnamed: R50.1, R66.2, U34.6
unnamed: R51.1, R67.2, U34.13
unnamed: R52.1, R68.2, U34.9
unnamed: R53.1, R69.2, U35.2
unnamed: R54.1, R70.2, U35.6
unnamed: R55.1, R71.2, U35.13
unnamed: R56.1, R72.2, U35.9
unnamed: R57.1, R73.2, U36.2
unnamed: R58.1, R74.2, U36.6
unnamed: R59.1, R75.2, U36.13
unnamed: R60.1, R76.2, U36.9
unnamed: R77.1, R80.2, U37.2
unnamed: R78.1, R79.2, U37.6
unnamed: R81.1, R97.2, U38.2
unnamed: R82.1, R98.2, U38.6
unnamed: R83.1, R99.2, U38.13
unnamed: R84.1, R100.2, U38.9
unnamed: R85.1, R101.2, U39.2
unnamed: R86.1, R102.2, U39.6
unnamed: R87.1, R103.2, U39.13
unnamed: R88.1, R104.2, U39.9
unnamed: R89.1, R105.2, U40.2
unnamed: R90.1, R106.2, U40.6
unnamed: R91.1, R107.2, U40.13
unnamed: R92.1, R108.2, U40.9
unnamed: R93.1, R109.2, U41.2
unnamed: R94.1, R110.2, U41.6
unnamed: R95.1, R111.2, U41.13
unnamed: R96.1, R112.2, U41.9
unnamed: R113.1, R116.2, U42.2
unnamed: R114.1, R115.2, U42.6
unnamed: R117.1, R133.2, U43.2
unnamed: R118.1, R134.2, U43.6
unnamed: R119.1, R135.2, U43.13
unnamed: R120.1, R136.2, U43.9
unnamed: R121.1, R137.2, U44.2
unnamed: R122.1, R138.2, U44.6
unnamed: R123.1, R139.2, U44.13
unnamed: R124.1, R140.2, U44.9
unnamed: R125.1, R141.2, U45.2
unnamed: R126.1, R142.2, U45.6
unnamed: R127.1, R143.2, U45.13
unnamed: R128.1, R144.2, U45.9
unnamed: R129.1, R145.2, U46.2
unnamed: R130.1, R146.2, U46.6
unnamed: R131.1, R147.2, U46.13
unnamed: R132.1, R148.2, U46.9
unnamed: R149.1, R152.2, U47.2
unnamed: R150.1, R151.2, U47.6
unnamed: R153.1, R169.2, U48.2
unnamed: R154.1, R170.2, U48.6
unnamed: R155.1, R171.2, U48.13
unnamed: R156.1, R172.2, U48.9
unnamed: R157.1, R173.2, U49.2
unnamed: R158.1, R174.2, U49.6
unnamed: R159.1, R175.2, U49.13
unnamed: R160.1, R176.2, U49.9
unnamed: R161.1, R177.2, U50.2
unnamed: R162.1, R178.2, U50.6
unnamed: R163.1, R179.2, U50.13
unnamed: R164.1, R180.2, U50.9
unnamed: R165.1, R181.2, U51.2
unnamed: R166.1, R182.2, U51.6
unnamed: R167.1, R183.2, U51.13
unnamed: R168.1, R184.2, U51.9
unnamed: R185.1, R188.2, U52.2
unnamed: R186.1, R187.2, U52.6
unnamed: R189.1, R205.2, U53.2
unnamed: R190.1, R206.2, U53.6
unnamed: R191.1, R207.2, U53.13
unnamed: R192.1, R208.2, U53.9
unnamed: R193.1, R209.2, U54.2
unnamed: R194.1, R210.2, U54.6
unnamed: R195.1, R211.2, U54.13
unnamed: R196.1, R212.2, U54.9
unnamed: R197.1, R213.2, U55.2
unnamed: R198.1, R214.2, U55.6
unnamed: R199.1, R215.2, U55.13
unnamed: R200.1, R216.2, U55.9
unnamed: R201.1, R217.2, U56.2
unnamed: R202.1, R218.2, U56.6
unnamed: R203.1, R219.2, U56.13
unnamed: R204.1, R220.2, U56.9
unnamed: R221.1, R224.2, U57.2
unnamed: R222.1, R223.2, U57.6
unnamed: R225.1, R241.2, U58.2
unnamed: R226.1, R242.2, U58.6
unnamed: R227.1, R243.2, U58.13
unnamed: R228.1, R244.2, U58.9
unnamed: R229.1, R245.2, U59.2
unnamed: R230.1, R246.2, U59.6
unnamed: R231.1, R247.2, U59.13
unnamed: R232.1, R248.2, U59.9
unnamed: R233.1, R249.2, U60.2
unnamed: R234.1, R250.2, U60.6
unnamed: R235.1, R251.2, U60.13
unnamed: R236.1, R252.2, U60.9
unnamed: R237.1, R253.2, U61.2
unnamed: R238.1, R254.2, U61.6
unnamed: R239.1, R255.2, U61.13
unnamed: R240.1, R256.2, U61.9
unnamed: R257.1, R260.2, U62.2
unnamed: R258.1, R259.2, U62.6
unnamed: R261.1, R277.2, U63.2
unnamed: R262.1, R278.2, U63.6
unnamed: R263.1, R279.2, U63.13
unnamed: R264.1, R280.2, U63.9
unnamed: R265.1, R281.2, U64.2
unnamed: R266.1, R282.2, U64.6
unnamed: R267.1, R283.2, U64.13
unnamed: R268.1, R284.2, U64.9
unnamed: R269.1, R285.2, U65.2
unnamed: R270.1, R286.2, U65.6
unnamed: R271.1, R287.2, U65.13
unnamed: R272.1, R288.2, U65.9
unnamed: R273.1, R289.2, U66.2
unnamed: R274.1, R290.2, U66.6
unnamed: R275.1, R291.2, U66.13
unnamed: R276.1, R292.2, U66.9
unnamed: R293.1, R296.2, U67.2
unnamed: R294.1, R295.2, U67.6
unnamed: R297.1, R313.2, U68.2
unnamed: R298.1, R314.2, U68.6
unnamed: R299.1, R315.2, U68.13
unnamed: R300.1, R316.2, U68.9
unnamed: R301.1, R317.2, U69.2
unnamed: R302.1, R318.2, U69.6
unnamed: R303.1, R319.2, U69.13
unnamed: R304.1, R320.2, U69.9
unnamed: R305.1, R321.2, U70.2
unnamed: R306.1, R322.2, U70.6
unnamed: R307.1, R323.2, U70.13
unnamed: R308.1, R324.2, U70.9
unnamed: R309.1, R325.2, U71.2
unnamed: R310.1, R326.2, U71.6
unnamed: R311.1, R327.2, U71.13
unnamed: R312.1, R328.2, U71.9
